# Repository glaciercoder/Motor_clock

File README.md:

# Motor_clock

## Day 1:

看到了链接觉得很好玩，想自己搞一个。

首先考虑到静音的需求，企图使用小步进，配合TMC202x控制芯片来用。

感谢 *小山嘉* 提供步进电机链接，使用拆机小型步进，成本很低。

发现问题在于TMC202x成本过高。

考虑到每个电机只需要两个状态，打算使用双稳态电磁阀 

发现一个视频：

[Mechnical Design](httNs://www.youtube.com/watch?v=ukRGbEUAVtM&feature=youtu.be)

打算搞这个曲线就可以用最多6个电机完成控制。

## Day 2:

和 *李金时* 一起研究机械结构，发现一些问题

1. 如果将连杆固结在数字轴中心，，数字翻动时会导致连杆的上下运动，所以使用凸轮结构。
2. 发现上述视频里的方形数字有点儿丑，想采用菱形和梯形数字，但是菱形和梯形数字在转动时出现干涉的现象，所以对干涉的问题进行研究。

### 参数初步规定：

连杆内拉3mm从隐藏变为显示，杆直径2mm，凸轮壁厚1mm

### 凸轮设计：

记为放下状态(不显示)，为拉入状态（显示）

每$36^{\circ}$ 为一个变化时段，如果在该时段与下一时段交界处发生状态转变，则该时段最后$\Delta \theta$与下一时段$\Delta \theta$用于状态转变,对秒，$\Delta \theta = 10^{\circ}$;对分钟和小时,$\Delta \theta = 20^{\circ}$

| 编号/时序 |  1   | 2    | 3    | 4    | 5    | 6    | 7    | 8    | 9    | 0    |
| :-------: | :--: | ---- | ---- | ---- | ---- | ---- | ---- | ---- | ---- | ---- |
|     1     |  N   | P    | P    | N    | P    | P    | P    | P    | P    | P    |
|     2     |  P   | P    | P    | P    | N    | N    | P    | P    | P    | P    |
|     3     |  N   | P    | P    | P    | P    | P    | N    | P    | P    | N    |
|     4     |  N   | N    | N    | P    | P    | P    | N    | P    | P    | P    |
|     5     |  P   | N    | P    | P    | P    | P    | P    | P    | P    | P    |
|     6     |  N   | P    | P    | N    | P    | P    | N    | P    | P    | P    |
|     7     |  N   | P    | N    | N    | N    | P    | N    | P    | N    | P    |

利用上述表格进行绘图，思考一番决定使用Matlab多项式拟合极坐标方程，$10^{\circ}$给一个点

发现完全没有必要，直接拿sw做，过渡处使用两段切线弧过渡

在一番苦战之后，终于把凸轮搞定了，下面将基于该尺寸完善连杆机构

## Day 3:

开始着手设计PCB，打算先拿一个板子，把配置都配好，在最终控制板上不再使用引脚配置TMC2208，

可以使用的其他电机驱动（A4998 TB6612FNG）

### PCB Design

考虑到电机供电问题，考虑使用电池供电,可通过外接电源切换

考虑到凸轮转动方向不变，可以将DIR全部共起来，同时考虑到秒针，分针时针凸轮转动频率相同，使用6个PWM引脚就可以，用PCA9685 I2C模拟PWM

时钟使用DS3231

## Day 4:

 意识到电机数量太多，功率较高，需要考虑怎么画转换电路，感谢 *高一川 梁迪轩* 的帮助

发现PCA9685 I2C模拟PWM的问题：输出PWM的频率都是相同的，这无法用于步进电机控制，所以用PCA来处理时钟和分钟8路PWM，秒针单独用两路PWM

## Day 5

发现DC5525可以通过机械结构直接断开内部电路，不同担心转换电路了,但是考虑到一个问题是，如果电源不是从DC005拔掉而是从插线板拔掉就出问题？

## Day 6

先把电机调通搞一套初步能用的代码，再继续画板子。

TMC2208可以使用USART模式（高级设置），也可以是向A4988那样使用简单的PWM输入，打算使用后者。但是电机第一次没有成功起转。后来发现应该将PDN引脚拉低，同时EN与单片机GND连接。

电机转动不太正常，主要的可能是该步进电机的额定电流未知，没有设置的比较好，打算买好一点的电机，再进行调试。

#### 学习用热风枪焊接IC

锡量极其重要，不要放太多，不然引脚大概率粘接

风速不能太低，不然多余焊锡熔而不走，也容易造成粘接

## Day 7

把电机调好了，真坑爹啊，以后一定要看清文档，M1A，M1B接的是一个绕组

Arduino delayMicrosecond 是微秒！

和李金时看了第一版结构，余量不足，无法装配

发现使用PCA9685的问题：如果使用PCA9685内部时钟，漂移可能会非常严重，如果使用外部时钟，配置困难且难以保证I2C正常工作，最终决定将电机驱动直接挂在GPIO上

在kicad里修改完footprint需要开一个新的lib保存，不然可能无法生效

开始layout了

## Day 8

layout好了，有几个问题需要思考：电机开环如何复位

准备使用红外对管进行复位

对于接地问题的讨论[接地](http://blog.sina.com.cn/s/blog_6471e1bb0100mrjp.html)

## Day 9

打样测试

## Day 10

考虑代码构建，使用状态机

[参考](https://learn.adafruit.com/multi-tasking-the-arduino-part-1)

每个loop先判断状态，用flag标记每个电机状态，然后用在mills执行相应动作

对于不同位置的电机设置不同的interval实现转动速度的控制

需要设计不同的细分

[millis rollover](https://arduino.stackexchange.com/questions/12587/how-can-i-handle-the-millis-rollover/12588#12588)

考虑一种处理溢出的方法：手写高精度,但实际上

[This is not a problem](https://www.gammon.com.au/millis)

## Day11

处理归零问题，机械归零不太好，设计了一种对管的方案：

使用一个狭缝，对对管的发射进行限制，然后在转盘上设计狭窄突出，与狭缝配合，提高精度，但是考虑到读取精度可能不高，而且加工精度也达不到很高，遂放弃该方案

采用磁编码器，使用AS5600，考虑到淘宝没有能够适用电机尺寸的PCB，打算自己设计

打算使用角块的方式进行盒子的装配，这样可以使装配变得简单

AS5600 不能设I2C地址，无语子

貌似AS5600L可以，但是也没说怎么设？ 无语子

*高一川* 给出针对I2C无法修改地址的应对策略，使用TCA9548A，非常有价值

## Day 12

第一次设计的PCB到了，有一个元件没有贴，极其难受，先尝试烧录程序，并调试DS3231

第一版板子的问题：

LED_Pin不在PWM引脚，修改DIR

没贴全

USB画反了，USB有没有画反取决于引脚顺序，而不是外形

软件部分，buffer难以清空，想写一个依靠串口进行初始化的程序。

## Day 13

画AS5600pcb

修改第一版PCB，bug极多

1. ICSP接法：不是把一个的ICSP完全接到另一个的ICSP，targetRESET接法不一样！！！！！！需要接到10上
2. 不要在TX，RX上做LED，会让电压漂移
3. DTR必须接，不然不work，必须在DTR引脚到RESET之间串100nF电容，不然不work
4. CR3202 封装有问题

## Day14

调试第一版PCB，所用功能均正常

修改第一版PCB

1. 删去了DS3231的reset按钮，与MCU共RESET
2. PDN 直接接地
3. 加入了编码器接口
4. 加入蜂鸣器
5. 删去了无用的丝印
6. 修正了第一版的bug

机械装配遇到困难，采用数字板和连杆使用金属加工，其他部分3D打印的加工方式

## Day 15

讨论新的机械加工方案，打算使用齿轮传动，用固定座上的齿条驱动零件转动，但是加工仍然存在困难，考虑将元件放大两倍。

讨论盒子的设计方案

## Day 16

打印第二版零件，框加工有点儿贵，打算买现成的

南方小厂小批零件加工比北方大厂便宜很多，铝合金可直接激光切

## Day 17

调试第二版电路板，装配第二版机械零件。

第二版电路板控制部分工作正常，电源模块有问题，插上DC口出现烧坏的迹象，同时插入USB开始冒烟。4.7uH 电感挂了.

可能原因：电感许可电流太小，这是有可能的，在带LED之后确实需要比较大的电流输入，但是问题是没有接LED也挂了。 

六个电机接好，有一个不转，检查多次后无果，*夏博文* 提供帮助，发现是焊接connector时灌入过多的锡，导致connector在正面短路，焊接时一定要注意不能灌锡，应该尽量在一侧形成焊点。

六个编码器有一个不工作，怀疑是芯片的问题，打算重新做芯片

第三版软硬件修改：

1. 取消DS3231 RESET，实现一次上电一直记时的效果，对应的，把软件改成开机读取现在的时间，然后机械对钟。
2. 设置串口中断，只在接受到特定信号的时候进行DS3231设置
3. 将DIR换到非PWM引脚
4. 重画Buzzer电路，GPIO直接推不动

修改机械，使用内螺纹圆柱

内螺纹圆柱销 内径4x12x M3 100

M3x10 200个

## Day 18 19

重新修改机械结构，积累如下经验
==3D打印尽量设计螺丝固定等机构,尽可能少设计拼插==

==尽可能不要设计内槽道等结构，容易因为支撑等原因造成较大的误差==

==3D打印出的孔需要过一遍钻来保证精度==

==可以把层状3维结构拆分成2维，便于加工==

==sw建模使用树状装配体结构，将配合放在文件夹中便于修改，不要野配合==

==可以在适当的位置打孔，从而节省外包3D打印成本==

和李金时一起修3D打印机，

## Day 20
和nlc一起改了板子，主要是修改了电感的封装，新的板子功能正常。 <br/>
机械机构方面,nlc对齿条进行了两次修改，第一次延长了齿条长度，但是发现这个修改并不能解决啮合的问题，因此尝试将齿条整体抬高0.3mm，但是出现了上面的齿轮和齿条卡住的情况，对此，解决方案是把齿轮的高度下调一些。

## Day 21

- 发现一个大bug，凸轮结构控制滑块，考虑到每一层轨道控制的滑块要顺延90度，对应的轨道应该也转90度。

## Day 22

- nlc对底座进行了加强，避免了因底座在受力的情况下发生弯曲进而导致滑齿。

- ylw同学为了降低摩擦力非法使用了WD40，特此通报批评。

- wbc同学在调试过程中烧坏TMC2208一枚，工程经验又++。

## Day 23

- 302的门开了，nlc与wbc组装了一个完整的数字，调试顺利，而且噪声比预想的小很多。TMC2209驱动板的扭矩还是足够的。
  
  (https://youtube.com/shorts/_J2np6-Vw0g?feature=share)
  
 - 依然存在的问题&解决方案

    - 齿轮偶尔存在打滑的现象，原因可能是铜柱松动。由于无法精确设计铜柱的孔径大小，决定在竖直方向开孔，用M3螺丝锁住铜柱

## Day 24

- 新打印了座子与滑块，存在如下问题：

  - 由于3D打印机打印竖直方向的孔误差很大，M3螺丝容易打滑，考虑的解决方案是减小孔径。
  
  - 由于之前钢柱没完全固定，所以没有发现滑块和齿轮啮合过于紧的问题，打算先打印出来组装看看电机扭矩够不够。如果电机扭矩不够就降低滑块高度。

### 资料整理

[机械结构设计](httNs://www.youtube.com/watch?v=ukRGbEUAVtM&feature=youtu.be)

[TMC2208驱动](https://wiki.fysetc.com)

[TMC 接线](https://blog.csdn.net/weixin_42740222/article/details/88637535)

[Arduino TMC2208 lib](https://www.arduino.cc/reference/en/libraries/tmc2208stepper/)

[PCA9685电路设计](https://wenku.baidu.com/view/826d0d257c1cfad6185fa75c.html)

[PCA Arduino](https://learn.adafruit.com/16-channel-pwm-servo-driver/hooking-it-up)

[转换电路](https://www.eet-china.com/mp/a33537.html)

[DC5525](https://ask.zol.com.cn/x/5491238.html)

[Pin Mapping](https://www.arduino.cc/en/Hacking/PinMapping168)

[ATmega 328P-AU](https://forum.arduino.cc/t/atmega328-au/550838)

[Adafruit](https://learn.adafruit.com)

[AS5600](https://ams.com/as5600#tab/description)

[AS5600L](https://ams.com/documents/20143/36005/AS5600L_DS000545_3-00.pdf/7ade6878-7a32-2294-b88d-479d50fab6de)

[TCA9548](https://learn.adafruit.com/adafruit-tca9548a-1-to-8-i2c-multiplexer-breakout/downloads)

[I2C上拉电阻](https://www.zlg.cn/ipc/article/detail/id/690.html)

### 开销

中性笔(x)

买电机驱动模块 6个(x)

Niextube

嘉里创元件费（x）

云汉芯城元件费(x)

板子（x）

转接头（x）

DS3231模块(第一次)

DS3231模块(第二次) 

3D打印（200）

TCA9548A 模块

TPS561208DDCR

AS560 芯片(第一次)(x)

AS5600 芯片(第二次)

TCA9548A 芯片（30）

立创商城元件(x)

LED板（x）

第二次机械加工（860）

金属动板 (150)

嘉立创邮寄元件：TPS561208DDCR，TCA9548A(x), CH340G(x), 

WS2812(3m)(x)

邮寄处理费(x)

老铁：

中午吃饭. 51.5 (x)

《网络是怎样连接的》 91.64(x)

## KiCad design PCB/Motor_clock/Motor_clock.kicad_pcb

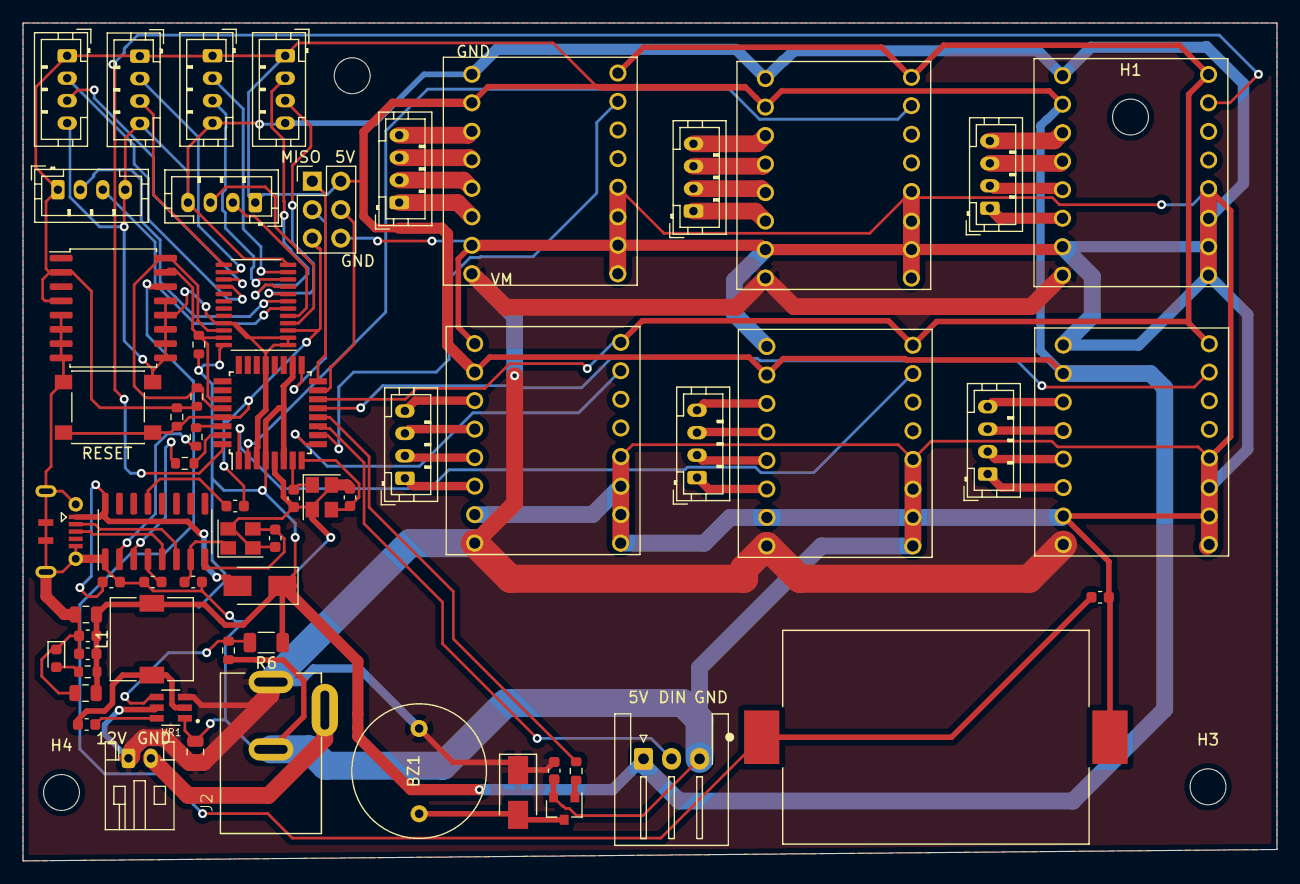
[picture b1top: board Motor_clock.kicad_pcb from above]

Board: 2 copper layers, 111.8 x 74.7 mm, 66 parts (0 on the bottom side), 75 nets.

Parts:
BT1: BT_3v3; TE_796136-1
BZ1: Buzzer; buzzer
C1: 100pF; C_0603_1608Metric
C2, C4: 1uF; C_0603_1608Metric
C3, C6, C11, C13: 22pF; C_0603_1608Metric
C5: 4.7uF; C_0805_2012Metric
C7: 22u; C_0805_2012Metric
C8: 0.1uF; C_0603_1608Metric
C9: 47uF; C_0805_2012Metric
C10: 10uF; C_0603_1608Metric
C12, C14, C15: 100nF; C_0603_1608Metric
D1: LED; LED_0603_1608Metric
D2, D3: 1N5819; D_SMA
H1, H2, H3, H4: MountingHole; MountingHole_3.2mm_M3
J1: WS2812; JST_XH_S3B-XH-A-1_1x03_P2.50mm_Horizontal
J2: Barrel_Jack_Switch; NINIGI_DC-005
J3: Battery_input; JST_PH_S2B-PH-K_1x02_P2.00mm_Horizontal
J4: ICSP; PinHeader_2x03_P2.54mm_Vertical
J5, J7: M_H_1; JST_PH_B4B-PH-K_1x04_P2.00mm_Vertical
J6: M_S_1; JST_PH_B4B-PH-K_1x04_P2.00mm_Vertical
J8: M_S_2; JST_PH_B4B-PH-K_1x04_P2.00mm_Vertical
J9: M_M_1; JST_PH_B4B-PH-K_1x04_P2.00mm_Vertical
J10: M_M_2; JST_PH_B4B-PH-K_1x04_P2.00mm_Vertical
J11: USB_B_Micro; MicroXNJ
J12: Enc_M_2; JST_PH_B4B-PH-K_1x04_P2.00mm_Vertical
J13: Enc_H_2; JST_PH_B4B-PH-K_1x04_P2.00mm_Vertical
J14: Enc_S_2; JST_PH_B4B-PH-K_1x04_P2.00mm_Vertical
J15: Enc_S_1; JST_PH_B4B-PH-K_1x04_P2.00mm_Vertical
J16: Enc_M1; JST_PH_B4B-PH-K_1x04_P2.00mm_Vertical
J17: Enc_H_1; JST_PH_B4B-PH-K_1x04_P2.00mm_Vertical
L1: 4.7uH; L_7.3x7.3_H4.5
Q1: Q_NPN_BEC; SOT-23
R1, R3, R4, R8, R9: 1k; R_0603_1608Metric
R2, R5: 4k7; R_0603_1608Metric
R6: 56.2k; R_1206_3216Metric
R7: 10k; R_0603_1608Metric
SW2: SW_Push; SW_Push_1P1T_NO_6x6mm_H9.5mm
U1: DS3231M; SOIC-16W_7.5x10.3mm_P1.27mm
U2: ATmega328P-AU; TQFP-32_7x7mm_P0.8mm
U3: M_H_1; TMC2208
U4: M_S_1; TMC2208
U5: M_H_2; TMC2208
U6: M_S_2; TMC2208
U7: M_M_1; TMC2208
U8: M_M_2; TMC2208
U9: CH340G; SOIC-16_3.9x9.9mm_P1.27mm
U10: TCA9548APWR; TSSOP-24_4.4x7.8mm_P0.65mm
VR1: TPS561208DDCR; SOT95P280X110-6N
Y1: 16Mhz; Crystal_SMD_3225-4Pin_3.2x2.5mm
Y2: 12Mhz; Crystal_SMD_3225-4Pin_3.2x2.5mm

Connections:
12V: BZ1.1 (-), C7.1, C15.1, D3.1 (K), J2.1, J3.1, U3.9 (VM), U4.9 (VM), U5.9 (VM), U6.9 (VM), U7.9 (VM), U8.9 (VM), VR1.3 (VIN), VR1.5 (EN)
+5V: C2.1, C4.1, C5.1, C9.1, D2.1 (K), J1.1, J4.2, J12.1, J13.1, J14.1, J15.1, J16.1, J17.1, L1.2, R1.1, R2.1, R5.1, R6.1, R8.1, U1.2 (VCC), U1.4 (~RST), U2.4 (VCC), U2.6 (VCC), U2.18 (AVCC), U3.15 (VIO), U4.15 (VIO), U5.15 (VIO), U6.15 (VIO), U7.15 (VIO), U8.15 (VIO), U10.24 (VCC)
BAT_GND: J2.2, J3.2
Buzzer: R9.2, U2.12 (PB0)
D+: J11.3 (D+), U9.5 (UD+)
D-: J11.2 (D-), U9.6 (UD-)
DIR: U2.14 (PB2), U3.8 (DIR), U4.8 (DIR), U5.8 (DIR), U6.8 (DIR), U7.8 (DIR), U8.8 (DIR)
LED_DA: J1.2, U2.11 (PD7)
MISO: J4.1, U2.16 (PB4)
MOSI: J4.4, U2.15 (PB3)
unnamed: BT1.1 (+), C1.1, U1.14 (VBAT)
unnamed: BZ1.2 (+), D3.2 (A), Q1.3 (C)
unnamed: C8.2, L1.1, VR1.2 (SW)
unnamed: C11.1, U9.7 (XI), Y2.1
unnamed: C12.1, U9.4 (V3)
unnamed: C13.1, U9.8 (XO), Y2.3
unnamed: C14.1, U9.13 (~DTR)
unnamed: D1.2 (A), R8.2
unnamed: J5.1, U3.11 (M1B)
unnamed: J5.2, U3.12 (M1A)
unnamed: J5.3, U3.13 (M2A)
unnamed: J5.4, U3.14 (M2B)
unnamed: J6.1, U4.11 (M1B)
unnamed: J6.2, U4.12 (M1A)
unnamed: J6.3, U4.13 (M2A)
unnamed: J6.4, U4.14 (M2B)
unnamed: J7.1, U5.11 (M1B)
unnamed: J7.2, U5.12 (M1A)
unnamed: J7.3, U5.13 (M2A)
unnamed: J7.4, U5.14 (M2B)
unnamed: J8.1, U6.11 (M1B)
unnamed: J8.2, U6.12 (M1A)
unnamed: J8.3, U6.13 (M2A)
unnamed: J8.4, U6.14 (M2B)
unnamed: J9.1, U7.11 (M1B)
unnamed: J9.2, U7.12 (M1A)
unnamed: J9.3, U7.13 (M2A)
unnamed: J9.4, U7.14 (M2B)
unnamed: J10.1, U8.11 (M1B)
unnamed: J10.2, U8.12 (M1A)
unnamed: J10.3, U8.13 (M2A)
unnamed: J10.4, U8.14 (M2B)
unnamed: Q1.1 (B), R9.1
unnamed: R3.2, U2.30 (PD0)
unnamed: R4.2, U2.31 (PD1)
P0: U2.13 (PB1), U3.7 (STEP)
P1: U2.32 (PD2), U5.7 (STEP)
P2: U2.1 (PD3), U7.7 (STEP)
P3: U2.2 (PD4), U8.7 (STEP)
P4: U2.9 (PD5), U4.7 (STEP)
P5: U2.10 (PD6), U6.7 (STEP)
PDN: BT1.2 (-), C1.2, C2.2, C3.1, C4.2, C5.2, C6.2, C7.2, C9.2, C10.2, C11.2, C12.2, C13.2, C15.2, D1.1 (K), J1.3, J2.3, J4.6, J11.5 (GND), J11.6 (Shield), J12.4, J13.4, J14.4, J15.4, J16.4, J17.4, Q1.2 (E), R7.2, SW2.1, U1.5 (GND), U1.6 (GND), U1.7 (GND), U1.8 (GND), U1.9 (GND), U1.10 (GND), U1.11 (GND), U1.12 (GND), U1.13 (GND), U2.3 (GND), U2.5 (GND), U2.21 (GND), U3.1 (EN), U3.2 (MS1), U3.3 (MS2), U3.4 (PDN), U3.10 (GND), U3.16 (GND), U4.1 (EN), U4.2 (MS1), U4.3 (MS2), U4.4 (PDN), U4.10 (GND), U4.16 (GND), U5.1 (EN), U5.2 (MS1), U5.3 (MS2), U5.4 (PDN), U5.10 (GND), U5.16 (GND), U6.1 (EN), U6.2 (MS1), U6.3 (MS2), U6.4 (PDN), U6.10 (GND), U6.16 (GND), U7.1 (EN), U7.2 (MS1), U7.3 (MS2), U7.4 (PDN), U7.10 (GND), U7.16 (GND), U8.1 (EN), U8.2 (MS1), U8.3 (MS2), U8.4 (PDN), U8.10 (GND), U8.16 (GND), U9.1 (GND), U10.1 (A0), U10.2 (A1), U10.12 (GND), U10.21 (A2), VR1.1 (GND), Y1.2, Y1.4, Y2.2, Y2.4
RESET: C14.2, J4.5, R1.2, SW2.2, U2.29 (~RESET/PC6), U10.3 (~RESET)
RX: R4.1, U9.3 (RXD)
SC0: J14.2, U10.5 (SC0)
SC1: J15.2, U10.7 (SC1)
SC2: J12.2, U10.9 (SC2)
SC3: J16.2, U10.11 (SC3)
SC4: J13.2, U10.14 (SC4)
SC5: J17.2, U10.16 (SC5)
SCK: J4.3, U2.17 (PB5)
SCL: R5.2, U1.16 (SCL), U2.28 (PC5), U10.22 (SCL)
SD0: J14.3, U10.4 (SD0)
SD1: J15.3, U10.6 (SD1)
SD2: J12.3, U10.8 (SD2)
SD3: J16.3, U10.10 (SD3)
SD4: J13.3, U10.13 (SD4)
SD5: J17.3, U10.15 (SD5)
SDA: R2.2, U1.15 (SDA), U2.27 (PC4), U10.23 (SDA)
TX: R3.1, U9.2 (TXD)
VBST: C8.1, VR1.6 (VBST)
VFB: R6.2, R7.1, VR1.4 (VFB)
VIN: C10.1, D2.2 (A), J11.1 (VBUS), U9.16 (VCC)
XTAL1: C3.2, U2.7 (XTAL1/PB6), Y1.1
XTAL2: C6.1, U2.8 (XTAL2/PB7), Y1.3

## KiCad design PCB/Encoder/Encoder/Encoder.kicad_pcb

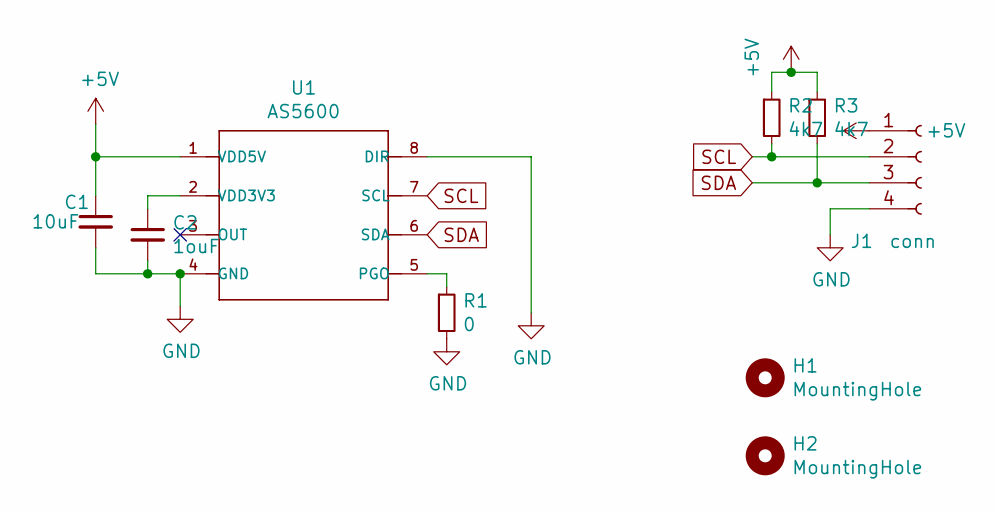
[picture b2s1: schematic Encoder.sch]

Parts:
C1: 10uF; C_0805_2012Metric
C2: 1ouF; C_0805_2012Metric
H1, H2: MountingHole; MountingHole_3.2mm_M3
J1: conn; JST_PH_B4B-PH-K_1x04_P2.00mm_Vertical
R1: 0; R_1206_3216Metric
R2, R3: 4k7; R_0603_1608Metric
U1: AS5600

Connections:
+5V: C1.1, J1.1, R2.1, R3.1, U1.1 (VDD5V)
GND: C1.2, C2.2, J1.4, R1.2, U1.4 (GND), U1.8 (DIR)
unnamed: C2.1, U1.2 (VDD3V3)
unnamed: R1.1, U1.5 (PGO)
SCL: J1.2, R2.2, U1.7 (SCL)
SDA: J1.3, R3.2, U1.6 (SDA)

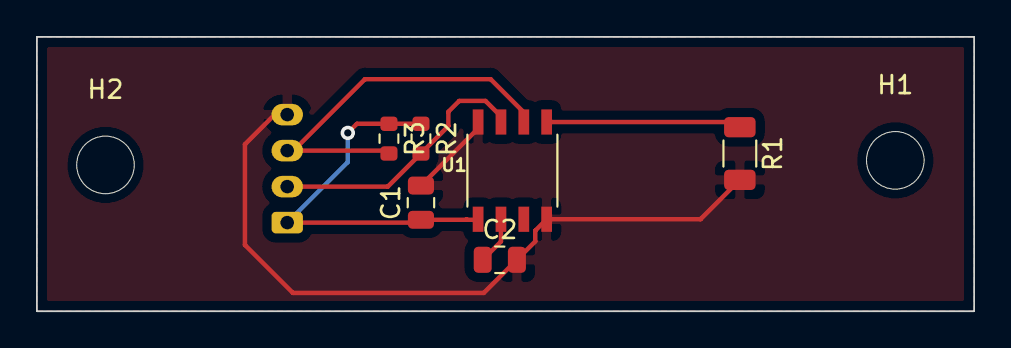
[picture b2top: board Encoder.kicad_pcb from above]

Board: 2 copper layers, 52.1 x 15.2 mm, 9 parts (1 on the bottom side), 6 nets.

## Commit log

2022-07-28 Bug fix
2022-07-28 Change the inductor
2022-08-01 Code
2022-08-01 Add readme
2022-08-02 Refatoring to oop
